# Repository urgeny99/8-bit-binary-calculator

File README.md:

# 8-bit-binary-calculator
## This is an 8-bit adder that adds two 8-bit numbers together (255+255).

### How It Works & Parts Used:

- 4x quad XOR gates (SN74HC86)
- 4x quad AND gates (SN74HC08)
- 2x quad OR gates (SN74HC32)
- 2x DIP switch x08
- 11x Decoupling capacitors 
- 9x single color LEDs for showing the output
- 25x resistors for setting switches Low and protecting LEDs (9x 1k; 16x 100k)
- 1x screw terminal for connecting to power

#### HOW IT WORKS

The adder works by having 8 + 8 inputs (A0-A7; B0-B7) and taking them into half and full adders.
Use the DIP-switches to set the input values, and read LED output.
The Half adder looks like this | And this is a Full adder 
:------:|:---------:
 | 

# BOM

Shematic   | PCB | 3D model
:-------------:|:-----------:|:-----------:
 |  |

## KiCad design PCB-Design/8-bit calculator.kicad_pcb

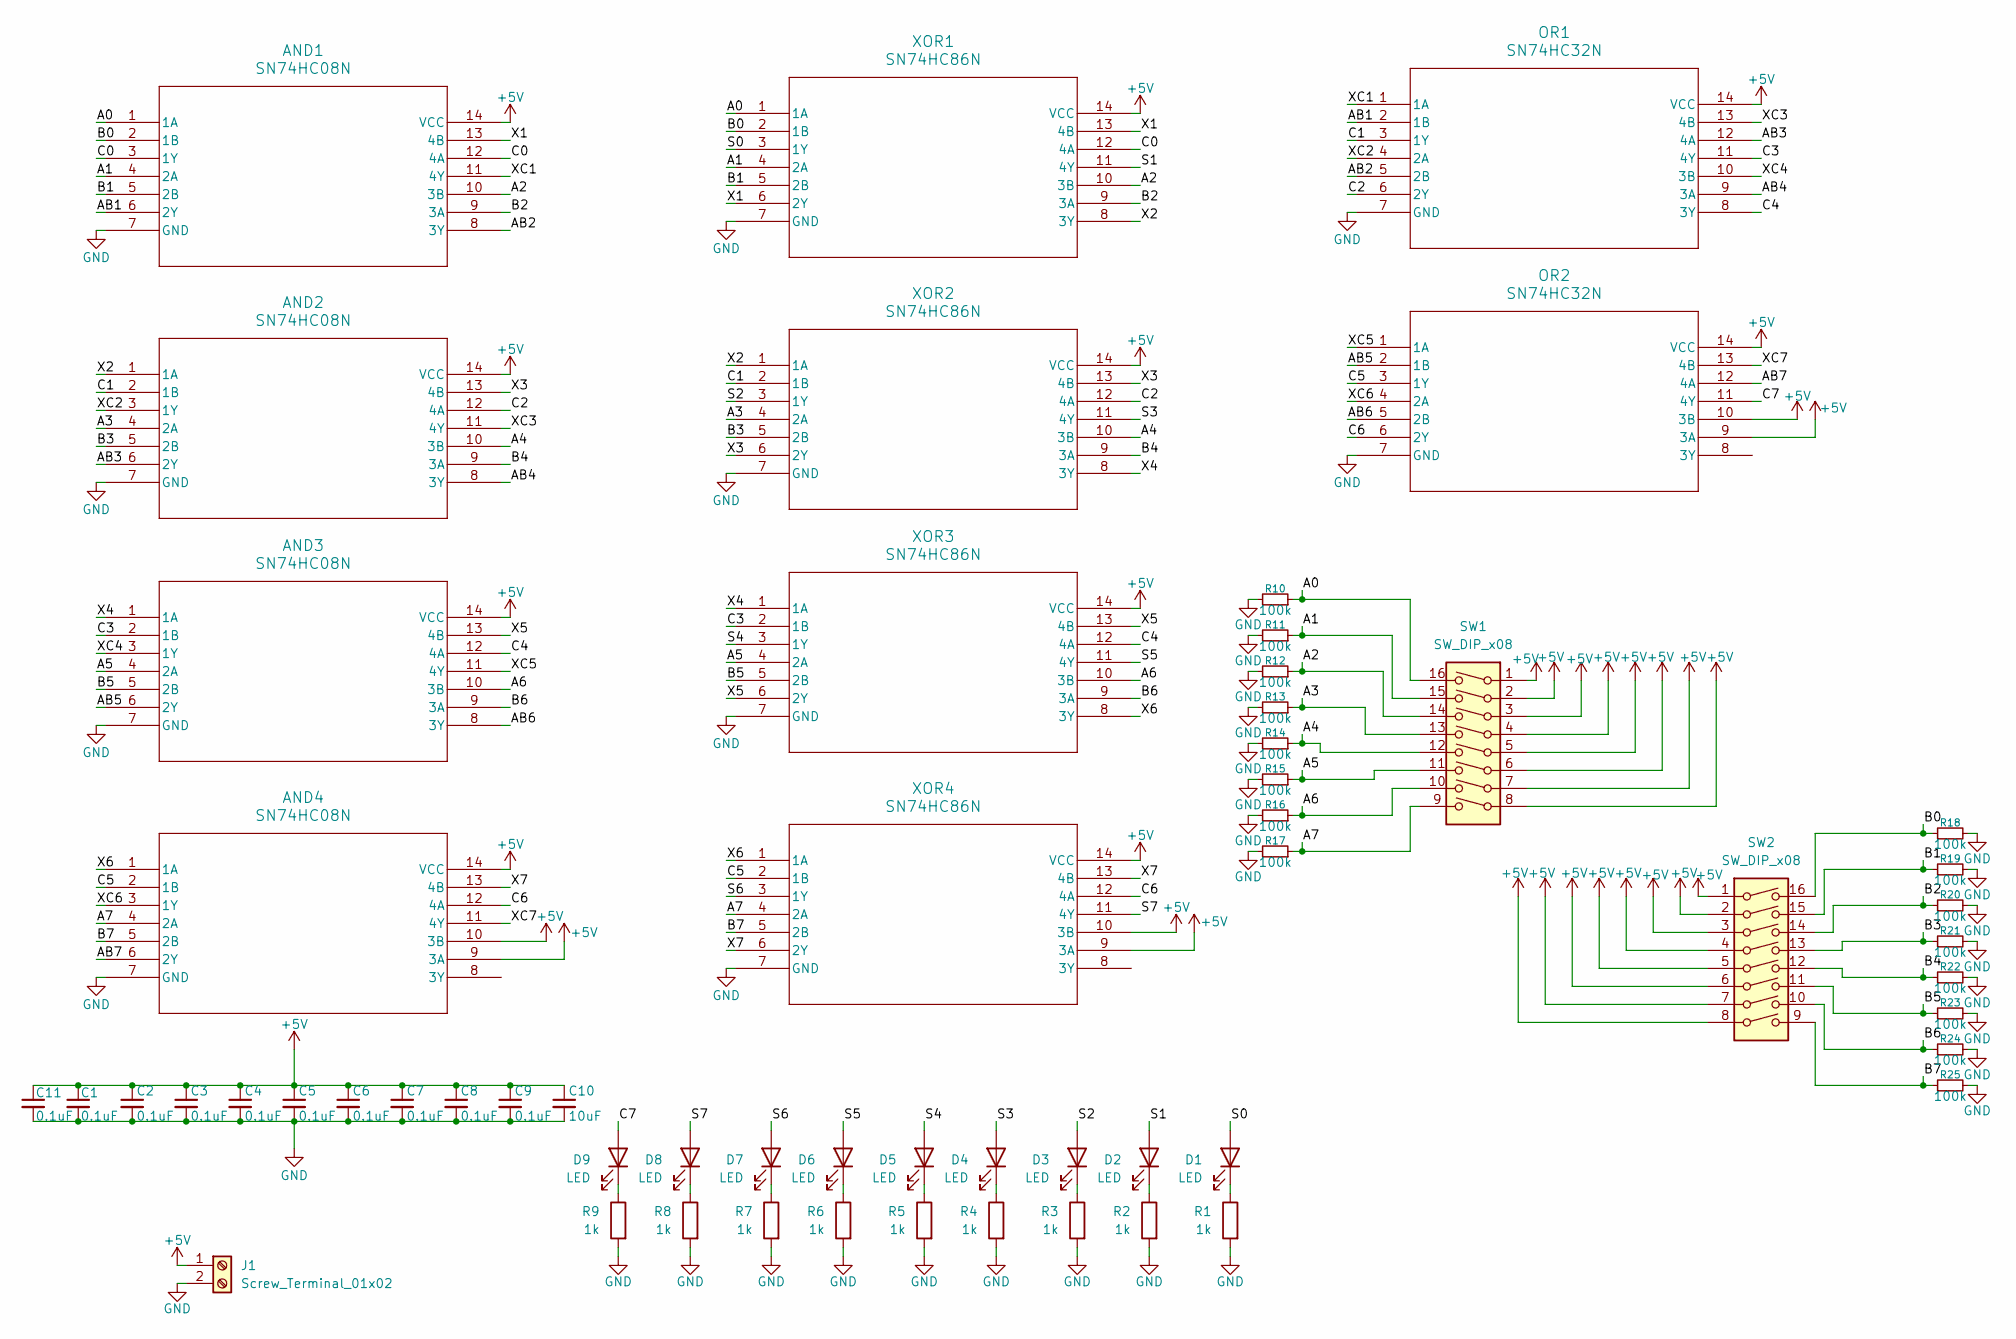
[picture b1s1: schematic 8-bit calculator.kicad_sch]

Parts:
AND1, AND2, AND3, AND4: SN74HC08N; SO-14_3.9x8.65mm_P1.27mm
C1, C2, C3, C4, C5, C6, C7, C8, C9, C11: 0.1uF; C_0603_1608Metric
C10: 10uF; C_0603_1608Metric
D1, D2, D3, D4, D5, D6, D7, D8, D9: LED; LED_0805_2012Metric
J1: Screw_Terminal_01x02; TerminalBlock_Phoenix_MKDS-1,5-2-5.08_1x02_P5.08mm_Horizont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
OR1, OR2: SN74HC32N; SO-14_3.9x8.65mm_P1.27mm
R1, R2, R3, R4, R5, R6, R7, R8, R9: 1k; R_0603_1608Metric
R10, R11, R12, R13, R14, R15, R16, R17, R18, R19, R20, R21, R22, R23, R24, R25: 100k; R_0603_1608Metric
SW1, SW2: SW_DIP_x08; SW_DIP_SPSTx08_Slide_9.78x22.5mm_W7.62mm_P2.54mm
XOR1, XOR2, XOR3, XOR4: SN74HC86N; SO-14_3.9x8.65mm_P1.27mm

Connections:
+5V: AND1.14 (VCC), AND2.14 (VCC), AND3.14 (VCC), AND4.9 (3A), AND4.10 (3B), AND4.14 (VCC), C1.1, C2.1, C3.1, C4.1, C5.1, C6.1, C7.1, C8.1, C9.1, C10.1, C11.1, J1.1, OR1.14 (VCC), OR2.9 (3A), OR2.10 (3B), OR2.14 (VCC), SW1.1, SW1.2, SW1.3, SW1.4, SW1.5, SW1.6, SW1.7, SW1.8, SW2.1, SW2.2, SW2.3, SW2.4, SW2.5, SW2.6, SW2.7, SW2.8, XOR1.14 (VCC), XOR2.14 (VCC), XOR3.14 (VCC), XOR4.9 (3A), XOR4.10 (3B), XOR4.14 (VCC)
/A0: AND1.1 (1A), R10.1, SW1.16, XOR1.1 (1A)
/A1: AND1.4 (2A), R11.1, SW1.15, XOR1.4 (2A)
/A2: AND1.10 (3B), R12.1, SW1.14, XOR1.10 (3B)
/A3: AND2.4 (2A), R13.1, SW1.13, XOR2.4 (2A)
/A4: AND2.10 (3B), R14.1, SW1.12, XOR2.10 (3B)
/A5: AND3.4 (2A), R15.1, SW1.11, XOR3.4 (2A)
/A6: AND3.10 (3B), R16.1, SW1.10, XOR3.10 (3B)
/A7: AND4.4 (2A), R17.1, SW1.9, XOR4.4 (2A)
/AB1: AND1.6 (2Y), OR1.2 (1B)
/AB2: AND1.8 (3Y), OR1.5 (2B)
/AB3: AND2.6 (2Y), OR1.12 (4A)
/AB4: AND2.8 (3Y), OR1.9 (3A)
/AB5: AND3.6 (2Y), OR2.2 (1B)
/AB6: AND3.8 (3Y), OR2.5 (2B)
/AB7: AND4.6 (2Y), OR2.12 (4A)
/B0: AND1.2 (1B), R18.1, SW2.16, XOR1.2 (1B)
/B1: AND1.5 (2B), R19.1, SW2.15, XOR1.5 (2B)
/B2: AND1.9 (3A), R20.1, SW2.14, XOR1.9 (3A)
/B3: AND2.5 (2B), R21.1, SW2.13, XOR2.5 (2B)
/B4: AND2.9 (3A), R22.1, SW2.12, XOR2.9 (3A)
/B5: AND3.5 (2B), R23.1, SW2.11, XOR3.5 (2B)
/B6: AND3.9 (3A), R24.1, SW2.10, XOR3.9 (3A)
/B7: AND4.5 (2B), R25.1, SW2.9, XOR4.5 (2B)
/C0: AND1.3 (1Y), AND1.12 (4A), XOR1.12 (4A)
/C1: AND2.2 (1B), OR1.3 (1Y), XOR2.2 (1B)
/C2: AND2.12 (4A), OR1.6 (2Y), XOR2.12 (4A)
/C3: AND3.2 (1B), OR1.11 (4Y), XOR3.2 (1B)
/C4: AND3.12 (4A), OR1.8 (3Y), XOR3.12 (4A)
/C5: AND4.2 (1B), OR2.3 (1Y), XOR4.2 (1B)
/C6: AND4.12 (4A), OR2.6 (2Y), XOR4.12 (4A)
/C7: D9.2 (A), OR2.11 (4Y)
/S0: D1.2 (A), XOR1.3 (1Y)
/S1: D2.2 (A), XOR1.11 (4Y)
/S2: D3.2 (A), XOR2.3 (1Y)
/S3: D4.2 (A), XOR2.11 (4Y)
/S4: D5.2 (A), XOR3.3 (1Y)
/S5: D6.2 (A), XOR3.11 (4Y)
/S6: D7.2 (A), XOR4.3 (1Y)
/S7: D8.2 (A), XOR4.11 (4Y)
/X1: AND1.13 (4B), XOR1.6 (2Y), XOR1.13 (4B)
/X2: AND2.1 (1A), XOR1.8 (3Y), XOR2.1 (1A)
/X3: AND2.13 (4B), XOR2.6 (2Y), XOR2.13 (4B)
/X4: AND3.1 (1A), XOR2.8 (3Y), XOR3.1 (1A)
/X5: AND3.13 (4B), XOR3.6 (2Y), XOR3.13 (4B)
/X6: AND4.1 (1A), XOR3.8 (3Y), XOR4.1 (1A)
/X7: AND4.13 (4B), XOR4.6 (2Y), XOR4.13 (4B)
/XC1: AND1.11 (4Y), OR1.1 (1A)
/XC2: AND2.3 (1Y), OR1.4 (2A)
/XC3: AND2.11 (4Y), OR1.13 (4B)
/XC4: AND3.3 (1Y), OR1.10 (3B)
/XC5: AND3.11 (4Y), OR2.1 (1A)
/XC6: AND4.3 (1Y), OR2.4 (2A)
/XC7: AND4.11 (4Y), OR2.13 (4B)
GND: AND1.7 (GND), AND2.7 (GND), AND3.7 (GND), AND4.7 (GND), C1.2, C2.2, C3.2, C4.2, C5.2, C6.2, C7.2, C8.2, C9.2, C10.2, C11.2, J1.2, OR1.7 (GND), OR2.7 (GND), R1.2, R2.2, R3.2, R4.2, R5.2, R6.2, R7.2, R8.2, R9.2, R10.2, R11.2, R12.2, R13.2, R14.2, R15.2, R16.2, R17.2, R18.2, R19.2, R20.2, R21.2, R22.2, R23.2, R24.2, R25.2, XOR1.7 (GND), XOR2.7 (GND), XOR3.7 (GND), XOR4.7 (GND)
unnamed: D1.1 (K), R1.1
unnamed: D2.1 (K), R2.1
unnamed: D3.1 (K), R3.1
unnamed: D4.1 (K), R4.1
unnamed: D5.1 (K), R5.1
unnamed: D6.1 (K), R6.1
unnamed: D7.1 (K), R7.1
unnamed: D8.1 (K), R8.1
unnamed: D9.1 (K), R9.1

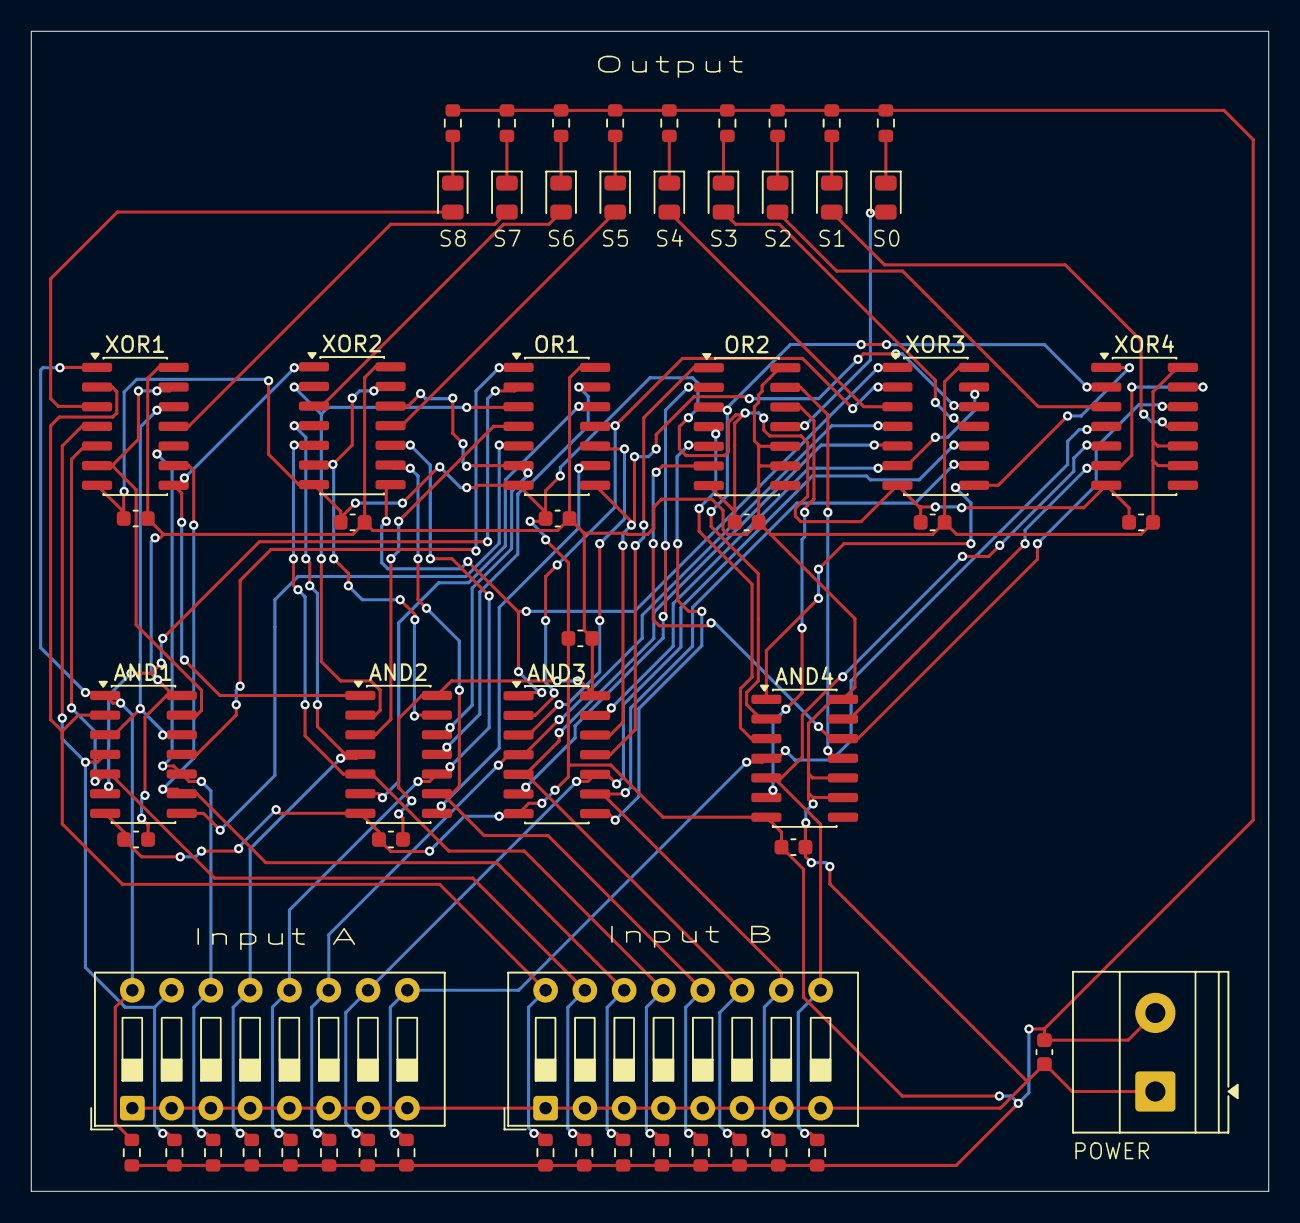
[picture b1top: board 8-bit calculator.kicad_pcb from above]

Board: 2 copper layers, 80.0 x 75.0 mm, 58 parts (0 on the bottom side), 64 nets.

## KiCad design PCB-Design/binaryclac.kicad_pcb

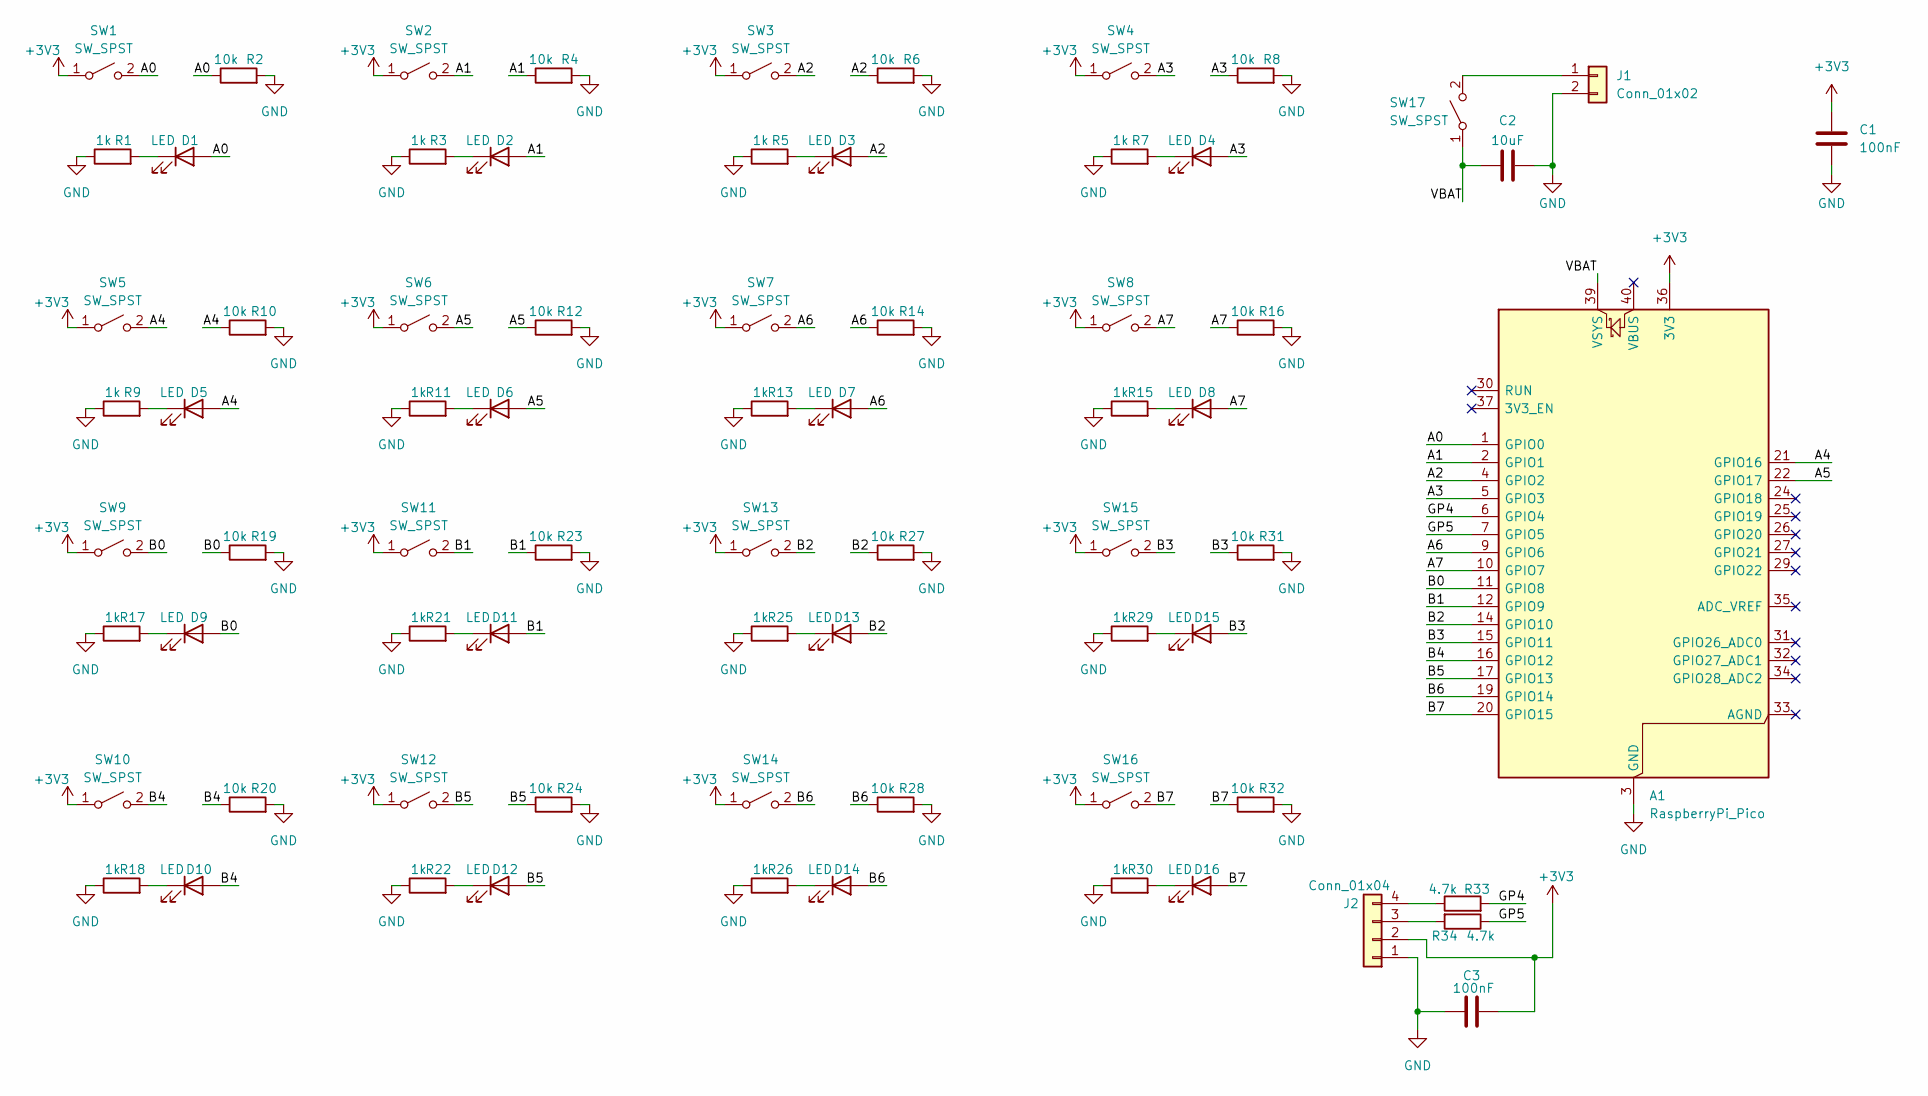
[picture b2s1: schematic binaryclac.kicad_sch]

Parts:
A1: RaspberryPi_Pico; RaspberryPi_Pico_Common_Unspecified
C1, C3: 100nF; C_Rect_L4.0mm_W2.5mm_P2.50mm
C2: 10uF; CP_Radial_D5.0mm_P2.00mm
D1, D2, D3, D4, D5, D6, D7, D8, D9, D10, D11, D12, D13, D14, D15, D16: LED; PinHeader_1x02_P2.54mm_Vertical
J1: Conn_01x02; PinHeader_1x02_P2.54mm_Vertical
J2: Conn_01x04; PinHeader_1x04_P2.54mm_Vertical
R1, R3, R5, R7, R9, R11, R13, R15, R17, R18, R21, R22, R25, R26, R29, R30: 1k; R_Axial_DIN0207_L6.3mm_D2.5mm_P7.62mm_Horizontal
R2, R4, R6, R8, R10, R12, R14, R16, R19, R20, R23, R24, R27, R28, R31, R32: 10k; R_Axial_DIN0207_L6.3mm_D2.5mm_P7.62mm_Horizontal
R33, R34: 4.7k; R_Axial_DIN0207_L6.3mm_D2.5mm_P7.62mm_Horizontal
SW1, SW2, SW3, SW4, SW5, SW6, SW7, SW8, SW9, SW10, SW11, SW12, SW13, SW14, SW15, SW16, SW17: SW_SPST; PinHeader_1x02_P2.54mm_Vertical

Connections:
+3V3: A1.36 (3V3), C1.2, C3.2, J2.2 (VCC), SW1.1 (A), SW2.1 (A), SW3.1 (A), SW4.1 (A), SW5.1 (A), SW6.1 (A), SW7.1 (A), SW8.1 (A), SW9.1 (A), SW10.1 (A), SW11.1 (A), SW12.1 (A), SW13.1 (A), SW14.1 (A), SW15.1 (A), SW16.1 (A)
/A0: A1.1 (GPIO0), D1.2 (A), R2.1, SW1.2 (B)
/A1: A1.2 (GPIO1), D2.2 (A), R4.1, SW2.2 (B)
/A2: A1.4 (GPIO2), D3.2 (A), R6.1, SW3.2 (B)
/A3: A1.5 (GPIO3), D4.2 (A), R8.1, SW4.2 (B)
/A4: A1.21 (GPIO16), D5.2 (A), R10.1, SW5.2 (B)
/A5: A1.22 (GPIO17), D6.2 (A), R12.1, SW6.2 (B)
/A6: A1.9 (GPIO6), D7.2 (A), R14.1, SW7.2 (B)
/A7: A1.10 (GPIO7), D8.2 (A), R16.1, SW8.2 (B)
/B0: A1.11 (GPIO8), D9.2 (A), R19.1, SW9.2 (B)
/B1: A1.12 (GPIO9), D11.2 (A), R23.1, SW11.2 (B)
/B2: A1.14 (GPIO10), D13.2 (A), R27.1, SW13.2 (B)
/B3: A1.15 (GPIO11), D15.2 (A), R31.1, SW15.2 (B)
/B4: A1.16 (GPIO12), D10.2 (A), R20.1, SW10.2 (B)
/B5: A1.17 (GPIO13), D12.2 (A), R24.1, SW12.2 (B)
/B6: A1.19 (GPIO14), D14.2 (A), R28.1, SW14.2 (B)
/B7: A1.20 (GPIO15), D16.2 (A), R32.1, SW16.2 (B)
/GP4: A1.6 (GPIO4), R33.2
/GP5: A1.7 (GPIO5), R34.1
/VBAT: A1.39 (VSYS), C2.1, SW17.1 (A)
GND: A1.3 (GND), A1.8 (GND), A1.13 (GND), A1.18 (GND), A1.23 (GND), A1.28 (GND), A1.38 (GND), C1.1, C2.2, C3.1, J1.2 (BAT-), J2.1 (GND), R1.1, R2.2, R3.1, R4.2, R5.1, R6.2, R7.1, R8.2, R9.1, R10.2, R11.1, R12.2, R13.1, R14.2, R15.1, R16.2, R17.1, R18.1, R19.2, R20.2, R21.1, R22.1, R23.2, R24.2, R25.1, R26.1, R27.2, R28.2, R29.1, R30.1, R31.2, R32.2
unnamed: D1.1 (K), R1.2
unnamed: D2.1 (K), R3.2
unnamed: D3.1 (K), R5.2
unnamed: D4.1 (K), R7.2
unnamed: D5.1 (K), R9.2
unnamed: D6.1 (K), R11.2
unnamed: D7.1 (K), R13.2
unnamed: D8.1 (K), R15.2
unnamed: D9.1 (K), R17.2
unnamed: D10.1 (K), R18.2
unnamed: D11.1 (K), R21.2
unnamed: D12.1 (K), R22.2
unnamed: D13.1 (K), R25.2
unnamed: D14.1 (K), R26.2
unnamed: D15.1 (K), R29.2
unnamed: D16.1 (K), R30.2
unnamed: J1.1 (BAT+), SW17.2 (B)
unnamed: J2.3 (SCK), R34.2
unnamed: J2.4 (SDA), R33.1

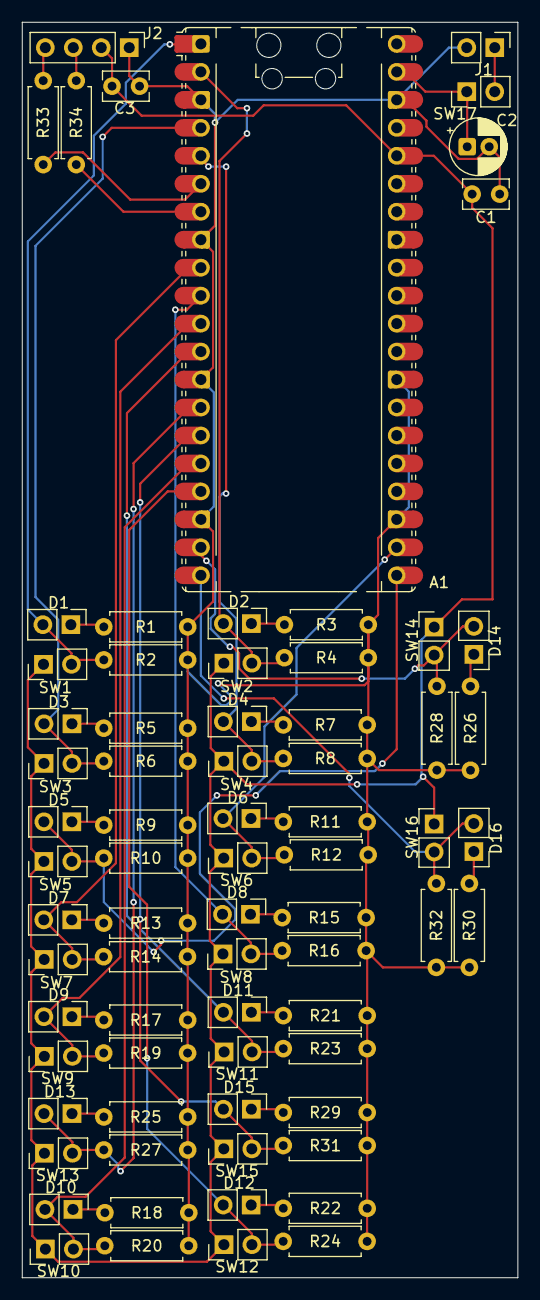
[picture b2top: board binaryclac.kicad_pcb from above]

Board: 2 copper layers, 45.0 x 114.0 mm, 73 parts (0 on the bottom side), 40 nets.

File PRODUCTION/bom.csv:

Designator,Footprint,Quantity,Value,LCSC Part #
A1,RaspberryPi_Pico_Common_Unspecified,1,RaspberryPi_Pico,
"C1, C3",C_Rect_L4.0mm_W2.5mm_P2.50mm,2,100nF,
C2,CP_Radial_D5.0mm_P2.00mm,1,10uF,
"D1, D10, D11, D12, D13, D14, D15, D16, D2, D3, D4, D5, D6, D7, D8, D9",PinHeader_1x02_P2.54mm_Vertical,16,LED,
J1,PinHeader_1x02_P2.54mm_Vertical,1,Conn_01x02,
J2,PinHeader_1x04_P2.54mm_Vertical,1,Conn_01x04,
"R1, R11, R13, R15, R17, R18, R21, R22, R25, R26, R29, R3, R30, R5, R7, R9",R_Axial_DIN0207_L6.3mm_D2.5mm_P7.62mm_Horizontal,16,1k,
"R10, R12, R14, R16, R19, R2, R20, R23, R24, R27, R28, R31, R32, R4, R6, R8",R_Axial_DIN0207_L6.3mm_D2.5mm_P7.62mm_Horizontal,16,10k,
"R33, R34",R_Axial_DIN0207_L6.3mm_D2.5mm_P7.62mm_Horizontal,2,4.7k,
"SW1, SW10, SW11, SW12, SW13, SW14, SW15, SW16, SW17, SW2, SW3, SW4, SW5, SW6, SW7, SW8, SW9",PinHeader_1x02_P2.54mm_Vertical,17,SW_SPST,

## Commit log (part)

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2026-02-02 Create PRODUCTION
2026-03-05 Clean up bom.csv formatting and remove empty lines
    Removed empty lines and adjusted formatting for consistency.
2026-03-05 Refactor bom.csv for formatting consistency
    Removed empty lines and adjusted formatting.
2026-03-05 Clean up bom.csv formatting and add missing commas
    Removed extra blank lines and added commas at the end of some lines.
2026-03-05 Fix formatting issues in bom.csv
2026-03-05 Clean up bom.csv formatting and remove blanks
    Removed extra blank lines and ensured consistent formatting.
2026-03-05 Fix BOM formatting and add missing parts
2026-03-05 Fix formatting and add missing URLs in bom.csv
2026-03-05 Update section title formatting in README
